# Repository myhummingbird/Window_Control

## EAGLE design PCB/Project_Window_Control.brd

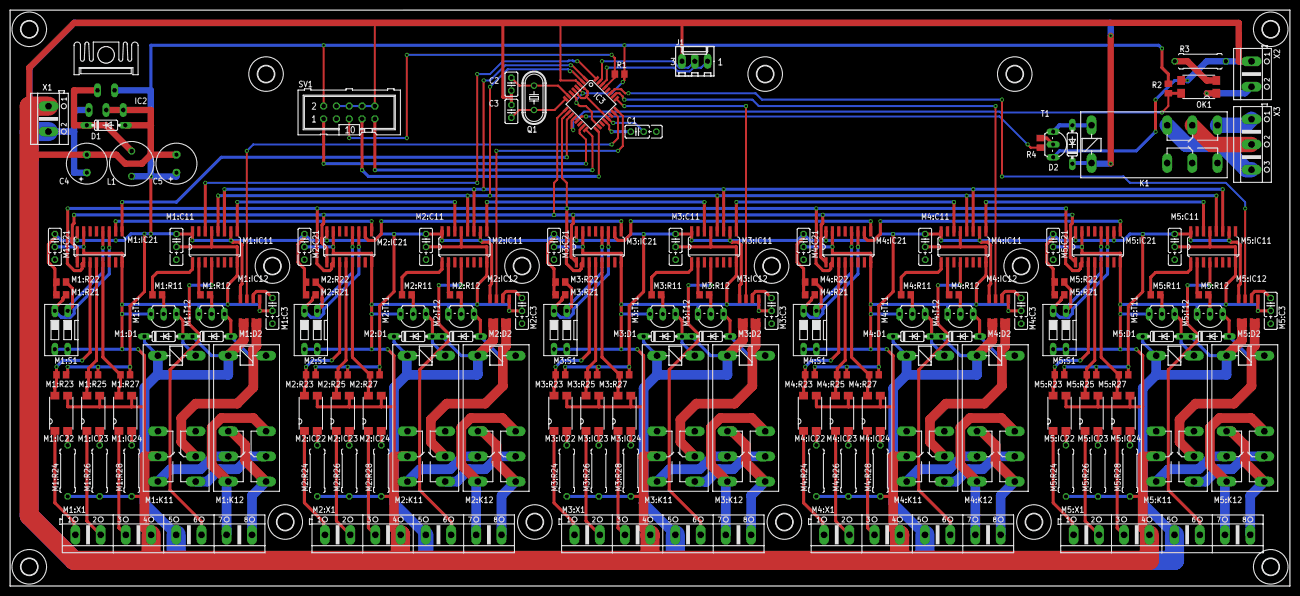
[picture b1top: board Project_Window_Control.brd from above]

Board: 2 copper layers, 254.0 x 114.3 mm, 174 parts (0 on the bottom side), 161 nets.

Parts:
C1: 100n; C025_050-025X075
C2, C3: 22p; C025-025X050
C4: 100uF/50V; E3,5-8
C5: 330uF/25V; E3,5-8
D1, D2: 1N5819; DO35-7
H1, H2, H3, H4, H5, H6, H7, H8, H9, H10, H11, H12, H13, H15, H16: MOUNT-HOLE3.3; 3,3
IC2: LM2575-5.0T; TO220-5
IC3: MEGA8-AI; TQFP32-08
J1: Debug; 6410-03
K1: FTR-F1CA024V; G2R2
KK1: SK95-2M3
L1: 330uH; 6000-XXXX-RC
M1:C3, M2:C3, M3:C3, M4:C3, M5:C3: 1n; C025_050-025X075
M1:C11, M1:C21, M2:C11, M2:C21, M3:C11, M3:C21, M4:C11, M4:C21, M5:C11, M5:C21: 100n; C025_050-025X075
M1:D1, M1:D2, M2:D1, M2:D2, M3:D1, M3:D2, M4:D1, M4:D2, M5:D1, M5:D2: 1N5819; DO35-7
M1:IC11, M2:IC11, M3:IC11, M4:IC11, M5:IC11: 74HC595D; SO16
M1:IC12, M2:IC12, M3:IC12, M4:IC12, M5:IC12: ACS712; SO08
M1:IC21, M2:IC21, M3:IC21, M4:IC21, M5:IC21: 74HC165D; SO16
M1:IC22, M1:IC23, M1:IC24, M2:IC22, M2:IC23, M2:IC24, M3:IC22, M3:IC23, M3:IC24, M4:IC22, M4:IC23, M4:IC24, M5:IC22, M5:IC23, M5:IC24: PC817; SMD4
M1:K11, M1:K12, M2:K11, M2:K12, M3:K11, M3:K12, M4:K11, M4:K12, M5:K11, M5:K12: FTR-F1CA024V; G2R2
M1:R11, M1:R12, M1:R21, M1:R22, M1:R23, M1:R25, M1:R27, M2:R11, M2:R12, M2:R21, M2:R22, M2:R23, M2:R25, M2:R27, M3:R11, M3:R12, M3:R21, M3:R22, M3:R23, M3:R25, M3:R27, M4:R11, M4:R12, M4:R21, M4:R22, M4:R23, M4:R25, M4:R27, M5:R11, M5:R12, M5:R21, M5:R22, M5:R23, M5:R25, M5:R27: 1k; R0805
M1:R24, M1:R26, M2:R24, M2:R26, M3:R24, M3:R26, M4:R24, M4:R26, M5:R24, M5:R26: 1.2k/1W; 0309/10
M1:R28, M2:R28, M3:R28, M4:R28, M5:R28: 470/0.5W; 0309/10
M1:S1, M2:S1, M3:S1, M4:S1, M5:S1: DS-02
M1:T11, M1:T12, M2:T11, M2:T12, M3:T11, M3:T12, M4:T11, M4:T12, M5:T11, M5:T12: BC548; TO92-EBC
M1:X1, M2:X1, M3:X1, M4:X1, M5:X1: AK500/8
OK1: LTV816S; SMD4
Q1: 16MHz; HC49U-V
R1, R2, R4: 1k; R0805
R3: 470/0.5W; 0309/10
SV1: ML10
T1: BC548; TO92-EBC
X1, X2: AK500/2
X3: AK500/3

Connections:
!BAS_ALL: IC3.12, OK1.4, R2.2
!RESET: IC3.29, R1.1, SV1.5
+5V: C5.+, IC2.4, IC3.4, IC3.6, IC3.18, L1.2, M1:C11.1, M1:C21.1, M1:IC11.10, M1:IC11.16, M1:IC12.8, M1:IC21.16, M1:R21.1, M1:R22.1, M1:R23.1, M1:R25.1, M1:R27.1, M2:C11.1, M2:C21.1, M2:IC11.10, M2:IC11.16, M2:IC12.8, M2:IC21.16, M2:R21.1, M2:R22.1, M2:R23.1, M2:R25.1, M2:R27.1, M3:C11.1, M3:C21.1, M3:IC11.10, M3:IC11.16, M3:IC12.8, M3:IC21.16, M3:R21.1, M3:R22.1, M3:R23.1, M3:R25.1, M3:R27.1, M4:C11.1, M4:C21.1, M4:IC11.10, M4:IC11.16, M4:IC12.8, M4:IC21.16, M4:R21.1, M4:R22.1, M4:R23.1, M4:R25.1, M4:R27.1, M5:C11.1, M5:C21.1, M5:IC11.10, M5:IC11.16, M5:IC12.8, M5:IC21.10, M5:IC21.16, M5:R21.1, M5:R22.1, M5:R23.1, M5:R25.1, M5:R27.1, R1.2, R2.1, SV1.2
+24V: C4.+, D2.C, IC2.1, K1.1, M1:D1.C, M1:D2.C, M1:IC12.1, M1:IC12.2, M1:K11.1, M1:K12.1, M1:X1.5, M2:D1.C, M2:D2.C, M2:IC12.1, M2:IC12.2, M2:K11.1, M2:K12.1, M2:X1.5, M3:D1.C, M3:D2.C, M3:IC12.1, M3:IC12.2, M3:K11.1, M3:K12.1, M3:X1.5, M4:D1.C, M4:D2.C, M4:IC12.1, M4:IC12.2, M4:K11.1, M4:K12.1, M4:X1.5, M5:D1.C, M5:D2.C, M5:IC12.1, M5:IC12.2, M5:K11.1, M5:K12.1, M5:X1.5, X1.2
ALARM_ALL: IC3.13, R4.1
AN1: IC3.23, M1:IC12.7
AN2: IC3.24, M2:IC12.7
AN3: IC3.25, M3:IC12.7
AN4: IC3.26, M4:IC12.7
AN5: IC3.27, M5:IC12.7
BAS_ALL: OK1.1, X2.2
GND: C1.2, C2.2, C3.2, C4.-, C5.-, D1.A, IC2.3, IC2.5, IC3.3, IC3.5, IC3.21, J1.3, M1:C3.2, M1:C11.2, M1:C21.2, M1:IC11.8, M1:IC11.13, M1:IC12.5, M1:IC21.8, M1:IC21.15, M1:IC22.3, M1:IC23.3, M1:IC24.3, M1:K11.P2, M1:R24.2, M1:R26.2, M1:R28.2, M1:S1.3, M1:S1.4, M1:T11.E, M1:T12.E, M1:X1.4, M2:C3.2, M2:C11.2, M2:C21.2, M2:IC11.8, M2:IC11.13, M2:IC12.5, M2:IC21.8, M2:IC21.15, M2:IC22.3, M2:IC23.3, M2:IC24.3, M2:K11.P2, M2:R24.2, M2:R26.2, M2:R28.2, M2:S1.3, M2:S1.4, M2:T11.E, M2:T12.E, M2:X1.4, M3:C3.2, M3:C11.2, M3:C21.2, M3:IC11.8, M3:IC11.13, M3:IC12.5, M3:IC21.8, M3:IC21.15, M3:IC22.3, M3:IC23.3, M3:IC24.3, M3:K11.P2, M3:R24.2, M3:R26.2, M3:R28.2, M3:S1.3, M3:S1.4, M3:T11.E, M3:T12.E, M3:X1.4, M4:C3.2, M4:C11.2, M4:C21.2, M4:IC11.8, M4:IC11.13, M4:IC12.5, M4:IC21.8, M4:IC21.15, M4:IC22.3, M4:IC23.3, M4:IC24.3, M4:K11.P2, M4:R24.2, M4:R26.2, M4:R28.2, M4:S1.3, M4:S1.4, M4:T11.E, M4:T12.E, M4:X1.4, M5:C3.2, M5:C11.2, M5:C21.2, M5:IC11.8, M5:IC11.13, M5:IC12.5, M5:IC21.8, M5:IC21.15, M5:IC22.3, M5:IC23.3, M5:IC24.3, M5:K11.P2, M5:R24.2, M5:R26.2, M5:R28.2, M5:S1.3, M5:S1.4, M5:T11.E, M5:T12.E, M5:X1.4, OK1.3, R3.2, SV1.4, SV1.6, SV1.8, SV1.10, T1.E, X1.1, X2.1
I_CLK: IC3.10, M1:IC21.2, M2:IC21.2, M3:IC21.2, M4:IC21.2, M5:IC21.2
I_LATCH: IC3.9, M1:IC21.1, M2:IC21.1, M3:IC21.1, M4:IC21.1, M5:IC21.1
I_SEROUT: IC3.11, M1:IC21.9
M1:ALARM: M1:IC11.4, M1:X1.6
M1:BAS: M1:IC24.1, M1:X1.3
M1:MOTOR_A: M1:K12.O2, M1:K12.S1, M1:X1.8
M1:MOTOR_B: M1:K12.O1, M1:K12.S2, M1:X1.7
M1:N$1: M1:K11.S1, M1:K12.P1
M1:N$2: M1:K11.S2, M1:K12.P2
M1:N$3: M1:D1.A, M1:K11.2, M1:T11.C
M1:N$4: M1:R11.2, M1:T11.B
M1:N$5: M1:IC22.2, M1:R24.1
M1:N$6: M1:IC12.3, M1:IC12.4, M1:K11.P1
M1:N$7: M1:D2.A, M1:K12.2, M1:T12.C
M1:N$8: M1:R12.2, M1:T12.B
M1:N$9: M1:C3.1, M1:IC12.6
M1:N$10: M1:IC21.5, M1:IC24.4, M1:R27.2
M1:N$11: M1:IC21.3, M1:IC22.4, M1:R23.2
M1:N$12: M1:IC11.1, M1:R11.1
M1:N$13: M1:IC11.2, M1:R12.1
M1:N$15: M1:IC21.4, M1:IC23.4, M1:R25.2
M1:N$16: M1:IC23.2, M1:R26.1
M1:N$17: M1:IC24.2, M1:R28.1
M1:S_DOWN: M1:IC23.1, M1:X1.2
M1:S_SETTING: M1:IC21.11, M1:R21.2, M1:S1.2
M1:S_SETTING1: M1:IC21.12, M1:R22.2, M1:S1.1
M1:S_UP: M1:IC22.1, M1:X1.1
M2:ALARM: M2:IC11.4, M2:X1.6
M2:BAS: M2:IC24.1, M2:X1.3
M2:MOTOR_A: M2:K12.O2, M2:K12.S1, M2:X1.8
M2:MOTOR_B: M2:K12.O1, M2:K12.S2, M2:X1.7
M2:N$1: M2:K11.S1, M2:K12.P1
M2:N$2: M2:K11.S2, M2:K12.P2
M2:N$3: M2:D1.A, M2:K11.2, M2:T11.C
M2:N$4: M2:R11.2, M2:T11.B
M2:N$5: M2:IC22.2, M2:R24.1
M2:N$6: M2:IC12.3, M2:IC12.4, M2:K11.P1
M2:N$7: M2:D2.A, M2:K12.2, M2:T12.C
M2:N$8: M2:R12.2, M2:T12.B
M2:N$9: M2:C3.1, M2:IC12.6
M2:N$10: M2:IC21.5, M2:IC24.4, M2:R27.2
M2:N$11: M2:IC21.3, M2:IC22.4, M2:R23.2
M2:N$12: M2:IC11.1, M2:R11.1
M2:N$13: M2:IC11.2, M2:R12.1
M2:N$15: M2:IC21.4, M2:IC23.4, M2:R25.2
M2:N$16: M2:IC23.2, M2:R26.1
M2:N$17: M2:IC24.2, M2:R28.1
M2:S_DOWN: M2:IC23.1, M2:X1.2
M2:S_SETTING: M2:IC21.11, M2:R21.2, M2:S1.2
M2:S_SETTING1: M2:IC21.12, M2:R22.2, M2:S1.1
M2:S_UP: M2:IC22.1, M2:X1.1
M3:ALARM: M3:IC11.4, M3:X1.6
M3:BAS: M3:IC24.1, M3:X1.3
M3:MOTOR_A: M3:K12.O2, M3:K12.S1, M3:X1.8
M3:MOTOR_B: M3:K12.O1, M3:K12.S2, M3:X1.7
M3:N$1: M3:K11.S1, M3:K12.P1
M3:N$2: M3:K11.S2, M3:K12.P2
M3:N$3: M3:D1.A, M3:K11.2, M3:T11.C
M3:N$4: M3:R11.2, M3:T11.B
M3:N$5: M3:IC22.2, M3:R24.1
M3:N$6: M3:IC12.3, M3:IC12.4, M3:K11.P1
M3:N$7: M3:D2.A, M3:K12.2, M3:T12.C
M3:N$8: M3:R12.2, M3:T12.B
M3:N$9: M3:C3.1, M3:IC12.6
M3:N$10: M3:IC21.5, M3:IC24.4, M3:R27.2
M3:N$11: M3:IC21.3, M3:IC22.4, M3:R23.2
M3:N$12: M3:IC11.1, M3:R11.1
M3:N$13: M3:IC11.2, M3:R12.1
M3:N$15: M3:IC21.4, M3:IC23.4, M3:R25.2
M3:N$16: M3:IC23.2, M3:R26.1
M3:N$17: M3:IC24.2, M3:R28.1
M3:S_DOWN: M3:IC23.1, M3:X1.2
M3:S_SETTING: M3:IC21.11, M3:R21.2, M3:S1.2
M3:S_SETTING1: M3:IC21.12, M3:R22.2, M3:S1.1
M3:S_UP: M3:IC22.1, M3:X1.1
M4:ALARM: M4:IC11.4, M4:X1.6
M4:BAS: M4:IC24.1, M4:X1.3
M4:MOTOR_A: M4:K12.O2, M4:K12.S1, M4:X1.8
M4:MOTOR_B: M4:K12.O1, M4:K12.S2, M4:X1.7
M4:N$1: M4:K11.S1, M4:K12.P1
M4:N$2: M4:K11.S2, M4:K12.P2
M4:N$3: M4:D1.A, M4:K11.2, M4:T11.C
M4:N$4: M4:R11.2, M4:T11.B
M4:N$5: M4:IC22.2, M4:R24.1
M4:N$6: M4:IC12.3, M4:IC12.4, M4:K11.P1
M4:N$7: M4:D2.A, M4:K12.2, M4:T12.C
M4:N$8: M4:R12.2, M4:T12.B
M4:N$9: M4:C3.1, M4:IC12.6
M4:N$10: M4:IC21.5, M4:IC24.4, M4:R27.2
M4:N$11: M4:IC21.3, M4:IC22.4, M4:R23.2
M4:N$12: M4:IC11.1, M4:R11.1
M4:N$13: M4:IC11.2, M4:R12.1
M4:N$15: M4:IC21.4, M4:IC23.4, M4:R25.2
M4:N$16: M4:IC23.2, M4:R26.1
M4:N$17: M4:IC24.2, M4:R28.1
M4:S_DOWN: M4:IC23.1, M4:X1.2
M4:S_SETTING: M4:IC21.11, M4:R21.2, M4:S1.2
M4:S_SETTING1: M4:IC21.12, M4:R22.2, M4:S1.1
M4:S_UP: M4:IC22.1, M4:X1.1
M5:ALARM: M5:IC11.4, M5:X1.6
M5:BAS: M5:IC24.1, M5:X1.3
M5:MOTOR_A: M5:K12.O2, M5:K12.S1, M5:X1.8
M5:MOTOR_B: M5:K12.O1, M5:K12.S2, M5:X1.7
M5:N$1: M5:K11.S1, M5:K12.P1
M5:N$2: M5:K11.S2, M5:K12.P2
M5:N$3: M5:D1.A, M5:K11.2, M5:T11.C
M5:N$4: M5:R11.2, M5:T11.B
M5:N$5: M5:IC22.2, M5:R24.1
M5:N$6: M5:IC12.3, M5:IC12.4, M5:K11.P1
M5:N$7: M5:D2.A, M5:K12.2, M5:T12.C
M5:N$8: M5:R12.2, M5:T12.B
M5:N$9: M5:C3.1, M5:IC12.6
M5:N$10: M5:IC21.5, M5:IC24.4, M5:R27.2
M5:N$11: M5:IC21.3, M5:IC22.4, M5:R23.2
M5:N$12: M5:IC11.1, M5:R11.1
M5:N$13: M5:IC11.2, M5:R12.1
M5:N$15: M5:IC21.4, M5:IC23.4, M5:R25.2
M5:N$16: M5:IC23.2, M5:R26.1
M5:N$17: M5:IC24.2, M5:R28.1
M5:S_DOWN: M5:IC23.1, M5:X1.2
M5:S_SETTING: M5:IC21.11, M5:R21.2, M5:S1.2
M5:S_SETTING1: M5:IC21.12, M5:R22.2, M5:S1.1
M5:S_UP: M5:IC22.1, M5:X1.1
MISO: IC3.16, SV1.9
MOSI: IC3.15, SV1.1
unnamed: D2.A, K1.2, T1.C
unnamed: IC3.30, J1.1
unnamed: D1.C, IC2.2, L1.1
unnamed: R4.2, T1.B
unnamed: OK1.2, R3.1
unnamed: IC3.31, J1.2
unnamed: M4:IC21.10, M5:IC21.9
unnamed: M1:IC11.9, M2:IC11.14
unnamed: C3.1, IC3.8, Q1.2
unnamed: C2.1, IC3.7, Q1.1
unnamed: C1.1, IC3.20
unnamed: M3:IC21.10, M4:IC21.9
unnamed: M2:IC21.10, M3:IC21.9
unnamed: M2:IC11.9, M3:IC11.14
unnamed: M1:IC21.10, M2:IC21.9
unnamed: K1.S1, X3.1
unnamed: M3:IC11.9, M4:IC11.14
unnamed: M4:IC11.9, M5:IC11.14
unnamed: K1.O1, X3.3
unnamed: K1.P1, X3.2
O_CLK: IC3.1, M1:IC11.11, M2:IC11.11, M3:IC11.11, M4:IC11.11, M5:IC11.11
O_LATCH: IC3.2, M1:IC11.12, M2:IC11.12, M3:IC11.12, M4:IC11.12, M5:IC11.12
O_SERIN: IC3.32, M1:IC11.14
SCK: IC3.17, SV1.7

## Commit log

2018-11-05 Initial Commit!
2018-11-05 Add: Shift out to all 595
2018-11-05 Update: read hc165 and write to hc595
2018-11-05 Add: UART; Add: ADC;
2018-11-06 add: process input(config, up_down) with adc to control output(run, dir) on each channel
2018-11-06 add: debounce algorithm
2018-11-06 add: timer tick
2018-11-07 Change: Device=atmega88p and F_CPU=8000000 Test: Output and timer pass!
2018-11-08 Change: F_CPU to 16MHz , Baud = 38400 , Control_loop@20Hz Update: hc165 and test sw to control motor is ok! Update: enable adc fn but not test!
2018-11-11 update: adc sampling as interrupt
2018-11-11 Add: BAS control Add: Timeout for Motor Active
2018-11-18 Add: DiffAmp PCB Add: ICD wiring
2018-11-19 Update: Current Sense via DiffAmp
2018-11-21 Add: USBAsp driver and ICD for PCB-DiffAmp
2018-11-21 improve: summation current 6 times before check
2018-12-20 change: alarm will active when DIR_UP only
2019-07-02 Update DiffAmp.sch
    Add: Vout equation [ Vout = (R3/R1) * (V2 - V1)
